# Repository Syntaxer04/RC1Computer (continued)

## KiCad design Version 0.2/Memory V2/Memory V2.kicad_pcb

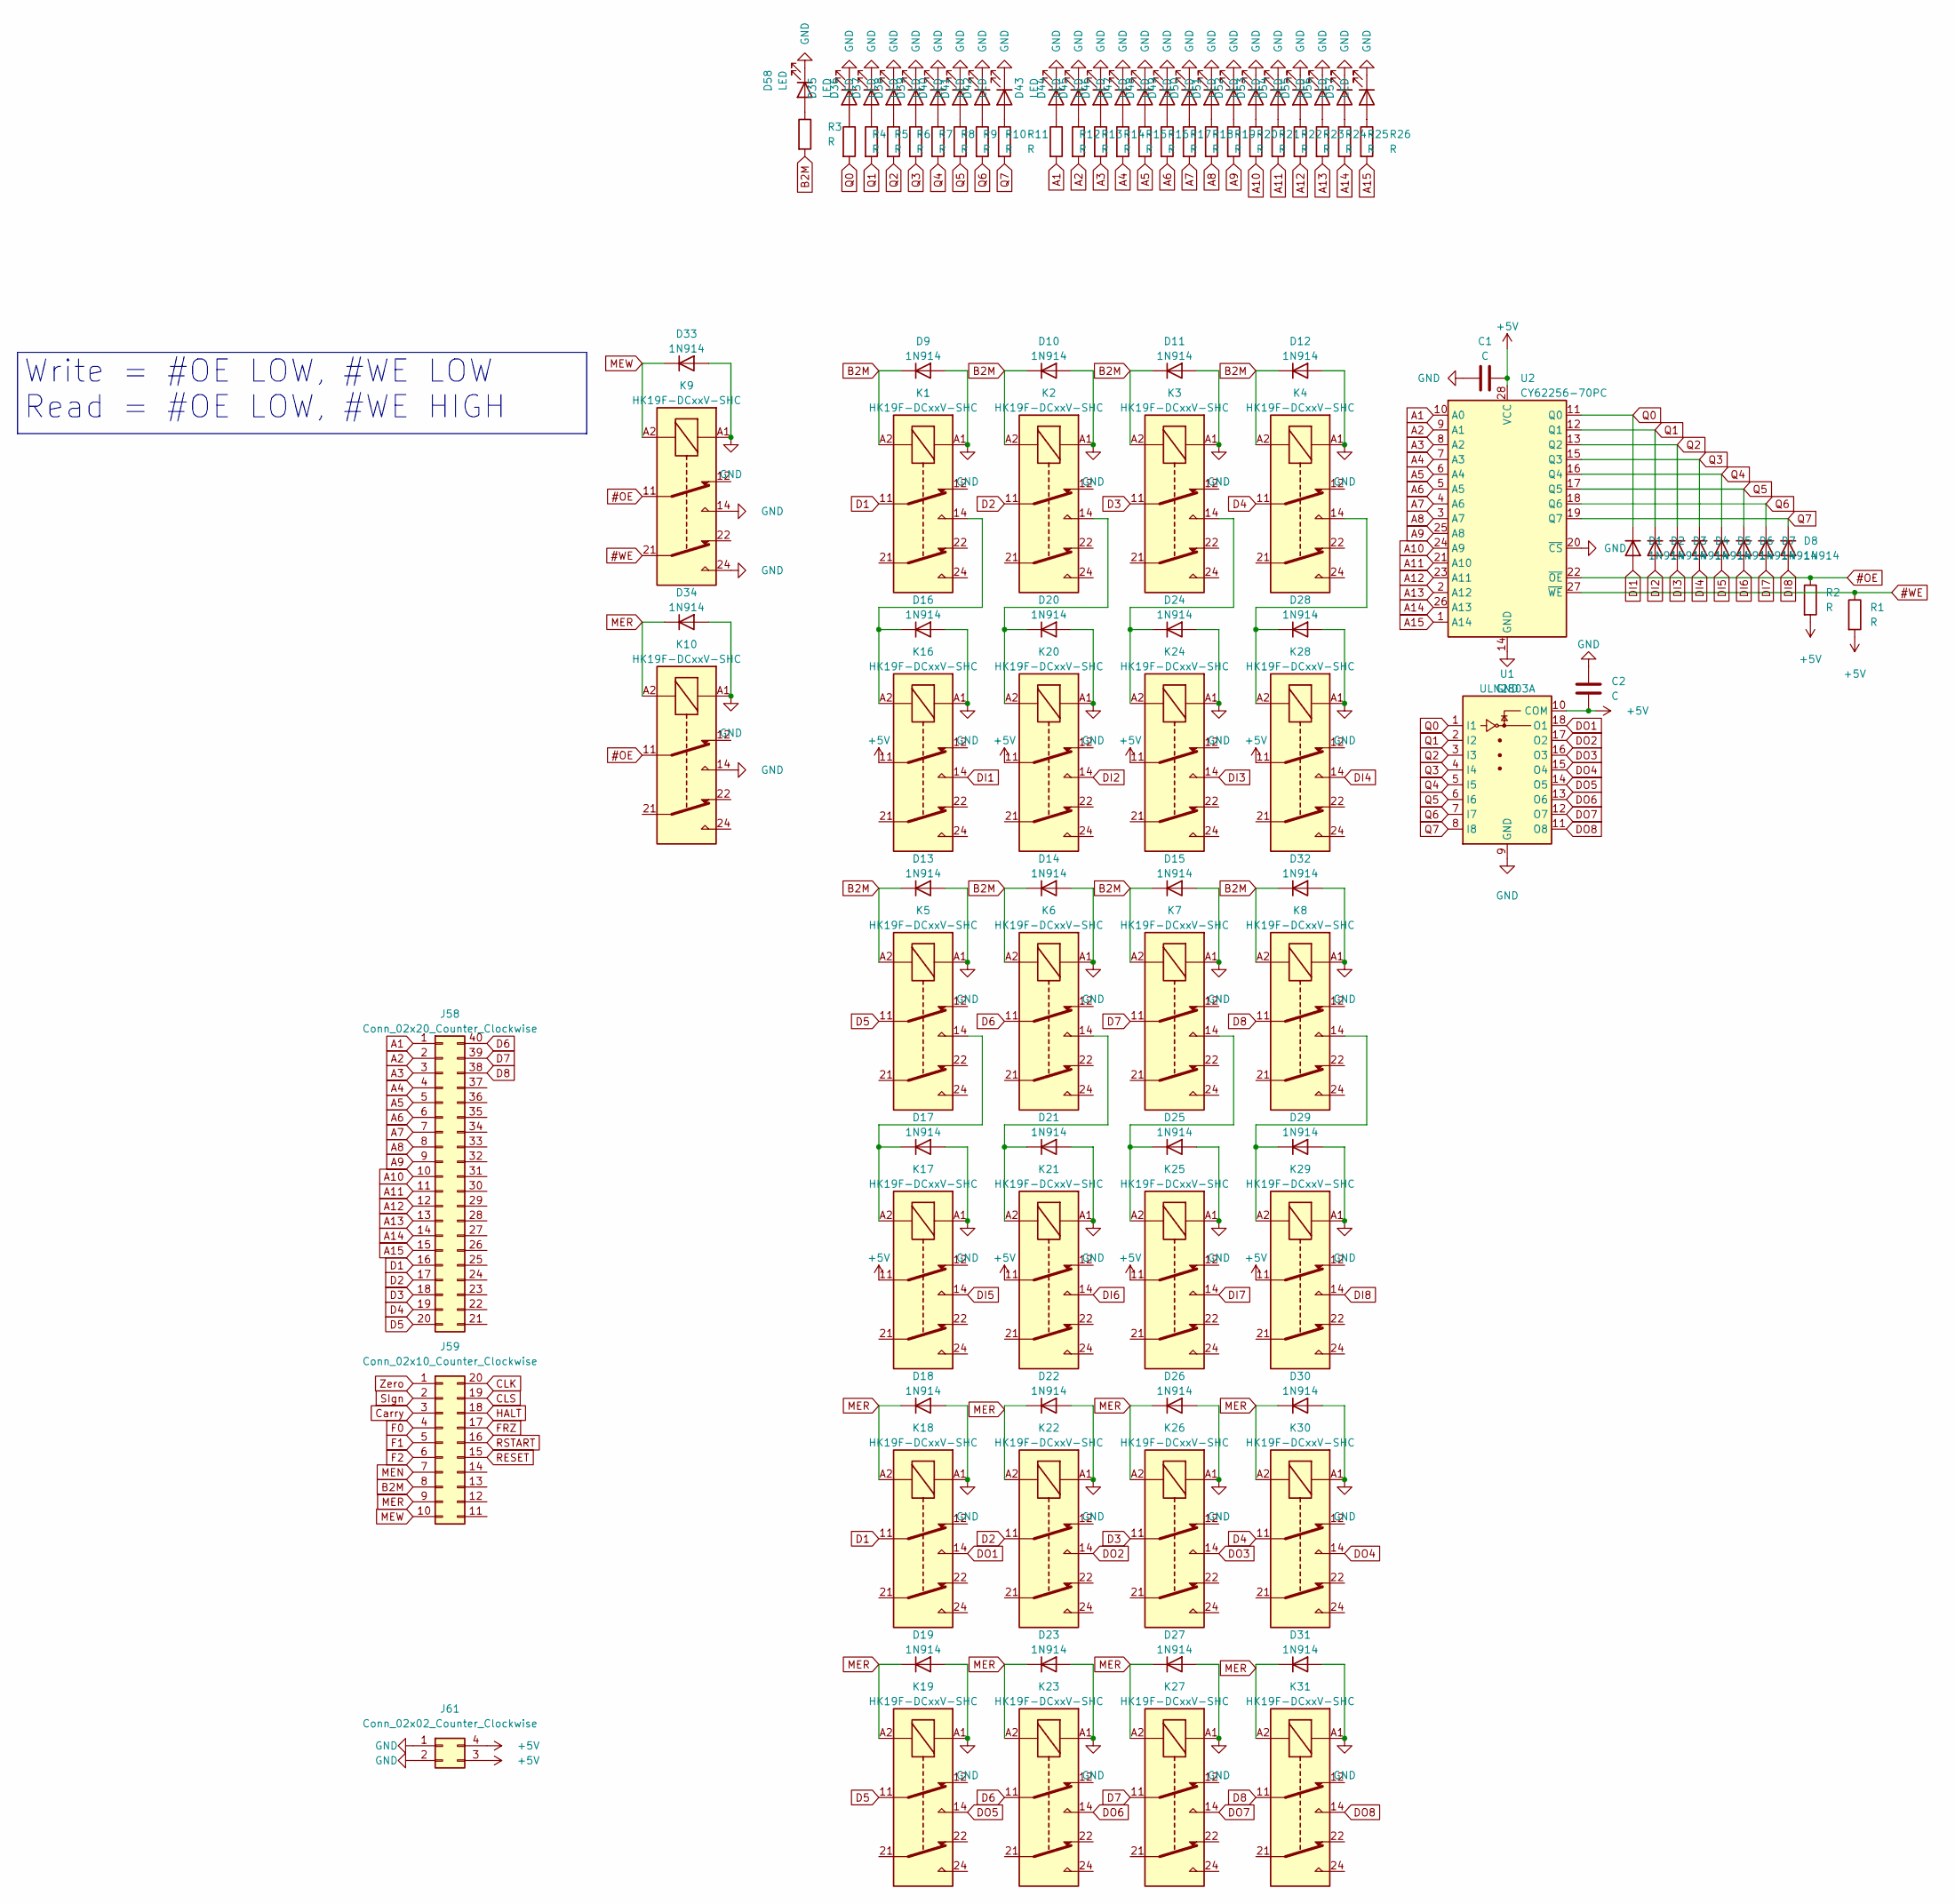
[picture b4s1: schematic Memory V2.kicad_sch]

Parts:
C1, C2: C; C_Radial_D6.3mm_H5.0mm_P2.50mm
D1, D2, D3, D4, D5, D6, D7, D8, D9, D10, D11, D12, D13, D14, D15, D16, D17, D18, D19, D20, D21, D22, D23, D24, D25, D26, D27, D28, D29, D30, D31, D32, D33, D34: 1N914; D_DO-35_SOD27_P7.62mm_Horizontal
D35, D36, D37, D38, D39, D40, D41, D42, D43, D44, D45, D46, D47, D48, D49, D50, D51, D52, D53, D54, D55, D56, D57, D58: LED; LED_D5.0mm ohne SilkS
J58: Conn_02x20_Counter_Clockwise; PinSocket_2x20_P2.54mm_Horizontal
J59: Conn_02x10_Counter_Clockwise; PinSocket_2x10_P2.54mm_Horizontal
J61: Conn_02x02_Counter_Clockwise; PinSocket_2x02_P2.54mm_Horizontal
K1, K2, K3, K4, K5, K6, K7, K8, K9, K10, K16, K17, K18, K19, K20, K21, K22, K23, K24, K25, K26, K27, K28, K29, K30, K31: HK19F-DCxxV-SHC; Relay_DPDT_Finder_30.22
R1, R2: R; R_Axial_DIN0207_L6.3mm_D2.5mm_P10.16mm_Horizontal
R3, R4, R5, R6, R7, R8, R9, R10, R11, R12, R13, R14, R15, R16, R17, R18, R19, R20, R21, R22, R23, R24, R25, R26: R; R_Axial_DIN0207_L6.3mm_D2.5mm_P2.54mm_Vertical
U1: ULN2803A; DIP-18_W7.62mm
U2: CY62256-70PC; DIP-28_W15.24mm

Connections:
#OE: K9.11, K10.11, R2.1, U2.22 (~OE)
#WE: K9.21, R1.1, U2.27 (~WE)
+5V: C1.2, C2.2, J61.3, J61.4, K16.11, K17.11, K20.11, K21.11, K24.11, K25.11, K28.11, K29.11, R1.2, R2.2, U1.10 (COM), U2.28 (VCC)
A1: J58.1, R12.2, U2.10 (A0)
A2: J58.2, R13.2, U2.9 (A1)
A3: J58.3, R14.2, U2.8 (A2)
A4: J58.4, R15.2, U2.7 (A3)
A5: J58.5, R16.2, U2.6 (A4)
A6: J58.6, R17.2, U2.5 (A5)
A7: J58.7, R18.2, U2.4 (A6)
A8: J58.8, R19.2, U2.3 (A7)
A9: J58.9, R20.2, U2.25 (A8)
A10: J58.10, R21.2, U2.24 (A9)
A11: J58.11, R22.2, U2.21 (A10)
A12: J58.12, R23.2, U2.23 (A11)
A13: J58.13, R24.2, U2.2 (A12)
A14: J58.14, R25.2, U2.26 (A13)
A15: J58.15, R26.2, U2.1 (A14)
B2M: D9.1 (K), D10.1 (K), D11.1 (K), D12.1 (K), D13.1 (K), D14.1 (K), D15.1 (K), D32.1 (K), J59.8, K1.A2, K2.A2, K3.A2, K4.A2, K5.A2, K6.A2, K7.A2, K8.A2, R3.2
CLK: J59.20
CLS: J59.19
Carry: J59.3
D1: J58.16, K1.11, K18.11
D2: J58.17, K2.11, K22.11
D3: J58.18, K3.11, K26.11
D4: J58.19, K4.11, K30.11
D5: J58.20, K5.11, K19.11
D6: J58.40, K6.11, K23.11
D7: J58.39, K7.11, K27.11
D8: J58.38, K8.11, K31.11
DI1: D1.2 (A), K16.14
DI2: D2.2 (A), K20.14
DI3: D3.2 (A), K24.14
DI4: D4.2 (A), K28.14
DI5: D5.2 (A), K17.14
DI6: D6.2 (A), K21.14
DI7: D7.2 (A), K25.14
DI8: D8.2 (A), K29.14
DO1: K18.14, U1.18 (O1)
DO2: K22.14, U1.17 (O2)
DO3: K26.14, U1.16 (O3)
DO4: K30.14, U1.15 (O4)
DO5: K19.14, U1.14 (O5)
DO6: K23.14, U1.13 (O6)
DO7: K27.14, U1.12 (O7)
DO8: K31.14, U1.11 (O8)
F0: J59.4
F1: J59.5
F2: J59.6
FRZ: J59.17
GND: C1.1, C2.1, D9.2 (A), D10.2 (A), D11.2 (A), D12.2 (A), D13.2 (A), D14.2 (A), D15.2 (A), D16.2 (A), D17.2 (A), D18.2 (A), D19.2 (A), D20.2 (A), D21.2 (A), D22.2 (A), D23.2 (A), D24.2 (A), D25.2 (A), D26.2 (A), D27.2 (A), D28.2 (A), D29.2 (A), D30.2 (A), D31.2 (A), D32.2 (A), D33.2 (A), D34.2 (A), D35.1 (K), D36.1 (K), D37.1 (K), D38.1 (K), D39.1 (K), D40.1 (K), D41.1 (K), D42.1 (K), D43.1 (K), D44.1 (K), D45.1 (K), D46.1 (K), D47.1 (K), D48.1 (K), D49.1 (K), D50.1 (K), D51.1 (K), D52.1 (K), D53.1 (K), D54.1 (K), D55.1 (K), D56.1 (K), D57.1 (K), D58.1 (K), J61.1, J61.2, K1.A1, K2.A1, K3.A1, K4.A1, K5.A1, K6.A1, K7.A1, K8.A1, K9.14, K9.24, K9.A1, K10.14, K10.A1, K16.A1, K17.A1, K18.A1, K19.A1, K20.A1, K21.A1, K22.A1, K23.A1, K24.A1, K25.A1, K26.A1, K27.A1, K28.A1, K29.A1, K30.A1, K31.A1, U1.9 (GND), U2.14 (GND), U2.20 (~CS)
HALT: J59.18
MEN: J59.7
MER: D18.1 (K), D19.1 (K), D22.1 (K), D23.1 (K), D26.1 (K), D27.1 (K), D30.1 (K), D31.1 (K), D34.1 (K), J59.9, K10.A2, K18.A2, K19.A2, K22.A2, K23.A2, K26.A2, K27.A2, K30.A2, K31.A2
MEW: D33.1 (K), J59.10, K9.A2
unnamed: D16.1 (K), K1.14, K16.A2
unnamed: D17.1 (K), K5.14, K17.A2
unnamed: D20.1 (K), K2.14, K20.A2
unnamed: D21.1 (K), K6.14, K21.A2
unnamed: D24.1 (K), K3.14, K24.A2
unnamed: D25.1 (K), K7.14, K25.A2
unnamed: D28.1 (K), K4.14, K28.A2
unnamed: D29.1 (K), K8.14, K29.A2
unnamed: D35.2 (A), R4.1
unnamed: D36.2 (A), R5.1
unnamed: D37.2 (A), R6.1
unnamed: D38.2 (A), R7.1
unnamed: D39.2 (A), R8.1
unnamed: D40.2 (A), R9.1
unnamed: D41.2 (A), R10.1
unnamed: D42.2 (A), R11.1
unnamed: D43.2 (A), R12.1
unnamed: D44.2 (A), R13.1
unnamed: D45.2 (A), R14.1
unnamed: D46.2 (A), R15.1
unnamed: D47.2 (A), R16.1
unnamed: D48.2 (A), R17.1
unnamed: D49.2 (A), R18.1
unnamed: D50.2 (A), R19.1
unnamed: D51.2 (A), R20.1
unnamed: D52.2 (A), R21.1
unnamed: D53.2 (A), R22.1
unnamed: D54.2 (A), R23.1
unnamed: D55.2 (A), R24.1
unnamed: D56.2 (A), R25.1
unnamed: D57.2 (A), R26.1
unnamed: D58.2 (A), R3.1
Q0: D1.1 (K), R4.2, U1.1 (I1), U2.11 (Q0)
Q1: D2.1 (K), R5.2, U1.2 (I2), U2.12 (Q1)
Q2: D3.1 (K), R6.2, U1.3 (I3), U2.13 (Q2)
Q3: D4.1 (K), R7.2, U1.4 (I4), U2.15 (Q3)
Q4: D5.1 (K), R8.2, U1.5 (I5), U2.16 (Q4)
Q5: D6.1 (K), R9.2, U1.6 (I6), U2.17 (Q5)
Q6: D7.1 (K), R10.2, U1.7 (I7), U2.18 (Q6)
Q7: D8.1 (K), R11.2, U1.8 (I8), U2.19 (Q7)
RESET: J59.15
RSTART: J59.16
SIgn: J59.2
Zero: J59.1

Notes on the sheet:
Write = #OE LOW, #WE LOW Read = #OE LOW, #WE HIGH

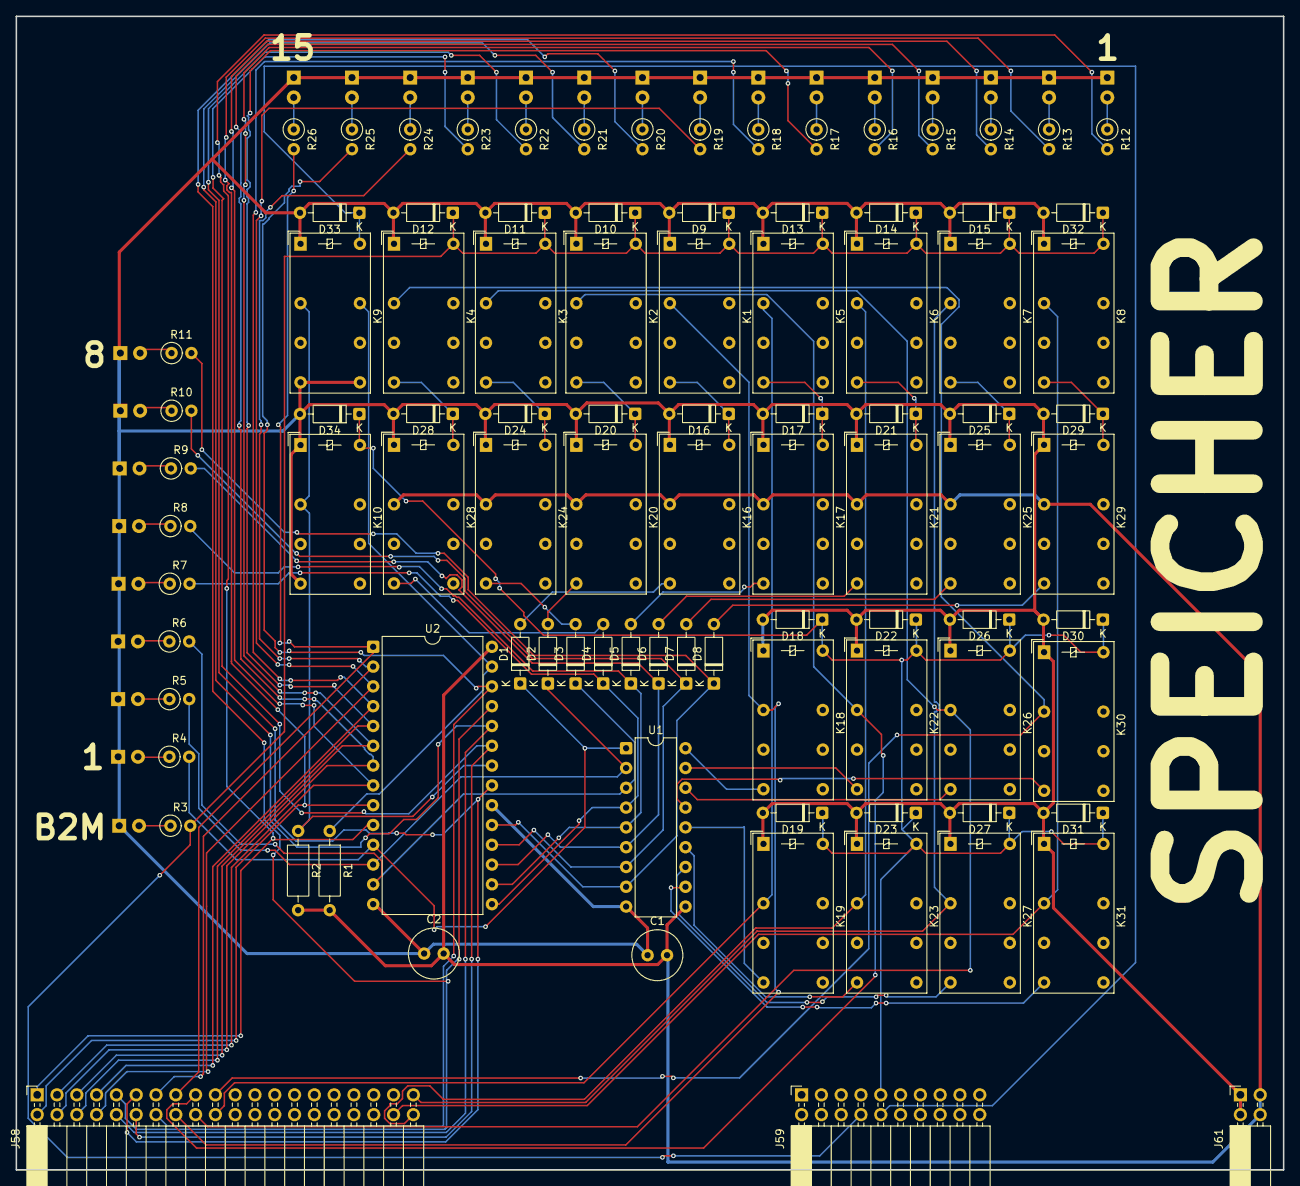
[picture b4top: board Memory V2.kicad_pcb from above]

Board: 2 copper layers, 162.6 x 148.0 mm, 117 parts (0 on the bottom side), 86 nets.
